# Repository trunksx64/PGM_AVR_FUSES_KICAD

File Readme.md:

# Restore AVR FUSES SMD ::: Revisión R1 :: Versión 1.10

## Razón de Ser e Inspiración

Este escudo para Arduino UNO se diseñó teniendo en mente inicialmente una forma para restaurar los FUSES del Atmega328P que por error u olvido se programaban mal en esta placa.
Haciendo inutilizables estos microcontroladores con programadores seriales como el AMTEL-ICE o MPLAB-SNAP, al inicio se diseñó como un simple restaurador, pero se vio la idea de dotarlo de más características como hacerlo un programador HIGH VOLTAJE, 
por lo cual se incluyo la etapa de elevación de tensión para obtener 12~14VDC, esta hizo que los pines disponibles del Arduino no fueran suficientes, se incluyo un expansor MCP23S08, para la comunicación de los Datos de 8Bits y el resto para el control de la programación en paralelo.
La idea a futuro es diseñar y crear una GUI multiplataforma para programar el Atmega328P y microcontroladores compatibles hacia abajo en número de pines.

## Características del Hardware

 * Socket ZIF de 28 Pines similar a la Marca 3M.
 * Expandor de puerto SPI MCP23S08.
 * Botones para Reset de la Placa UNO y Accion de programación.
 * Dos LEDS de estado de Programación.
 * Control de Alimentacion VCC y Elevador de Tensión para VPP.
 * Resistencias de protección, para evitar daño si el Microcontrolador es puesto al revez.
 * Diseño de Escudo (Shield) compatible con Arduino UNO R3.

## Características Específicas

Se tomó el Expansor MCP23S08, usando el protocolo SPI para garantizar la máxima velocidad de Datos para la Programación. 
El levador de tensión usa un juego de Diodo y Bobina simple, de fácil adquisición en el mercado con amplio valores sin problema alguno, todo esto implementado el control por PWM y ADC para controlar la estabilidad de la tensión de VPP para el microcontrolador.

## Versiones

* 2023 : 1.0.0 : Primera Versión.
* 2023 : 1.1.0 : Diseño de Liberias para Modelo 3D del Socket ZIF.

## ERRATAS

* Ninguna en el Momento.

## Créditos

xDNA Electronics & Desing es una microempresa Personal, que se dedica y encarga de elaborar proyectos de Control y Automatización por pedido, su idea es colaborar y ayudar a quines a si lo requieran, el proyecto se hizo principalmente como Hobby el cual gracias a terceros se pudo implementar y hacer su creación, por lo cual se da la libertad de usarlo para experimentar sin hacer uso comercial del mismo.

## Licencia

Licensed under Attribution-NonCommercial-ShareAlike 4.0 International (CC BY-NC-SA 4.0)

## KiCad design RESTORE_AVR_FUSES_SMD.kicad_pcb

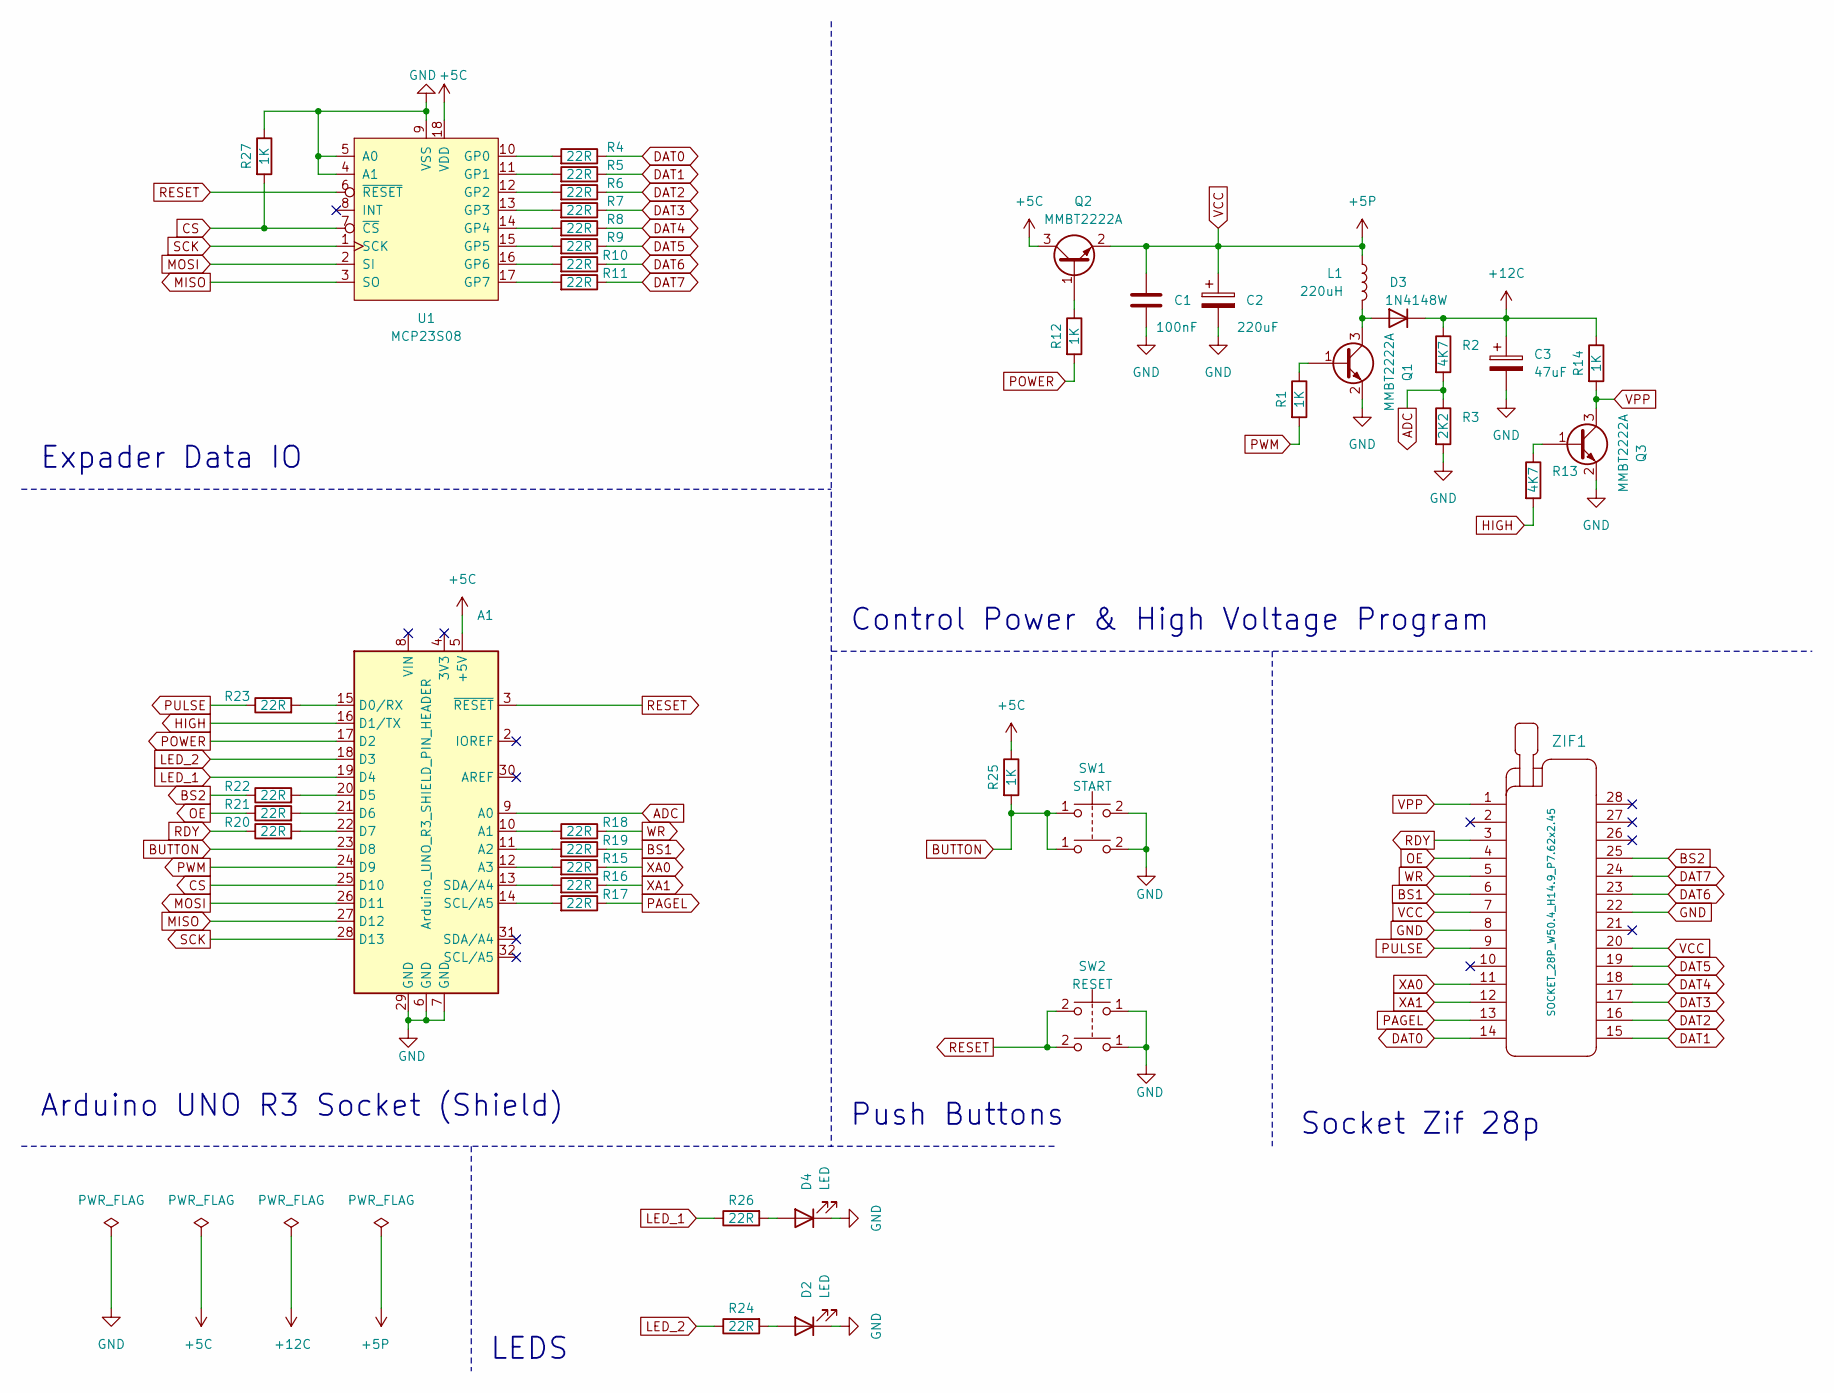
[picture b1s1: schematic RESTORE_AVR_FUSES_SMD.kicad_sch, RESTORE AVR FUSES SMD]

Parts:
A1: Arduino_UNO_R3_SHIELD_PIN_HEADER; x_Arduino_UNO_R3
C1: 100nF; C_1206_3216Metric
C2: 220uF; CP_Elec_6.3x5.2
C3: 47uF; CP_Elec_6.3x5.9
D2, D4: LED; LED_1210RVC
D3: 1N4148W; D_SOD-123
L1: 220uH; L_Sunlord_MWSA0402S
Q1, Q2, Q3: MMBT2222A; SOT-23
R1, R12, R14, R25, R27: 1K; R_1206_3216Metric_Pad1.30x1.75mm_HandSolder
R2, R13: 4K7; R_1206_3216Metric_Pad1.30x1.75mm_HandSolder
R3: 2K2; R_1206_3216Metric_Pad1.30x1.75mm_HandSolder
R4, R5, R6, R7, R8, R9, R10, R11, R15, R16, R17, R18, R19, R20, R21, R22, R23, R24, R26: 22R; R_1206_3216Metric_Pad1.30x1.75mm_HandSolder
SW1: START; SW_PUSH_6mm
SW2: RESET; SW_PUSH_6mm
U1: MCP23S08; SOIC-18W_7.5x11.6mm_P1.27mm
ZIF1: SOCKET_28P_W50.4_H14.9_P7.62x2.45

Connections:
+5C: A1.5 (+5V), Q2.3 (C), R25.1, U1.18 (VDD)
+12C: C3.1, D3.1 (K), R2.1, R14.1
ADC: A1.9 (A0), R2.2, R3.1
BS1: R19.1, ZIF1.6
BS2: R22.1, ZIF1.25
BUTTON: A1.23 (D8), R25.2, SW1.1
CS: A1.25 (D10), R27.2, U1.7 (~CS)
DAT0: R4.1, ZIF1.14
DAT1: R5.1, ZIF1.15
DAT2: R6.1, ZIF1.16
DAT3: R7.1, ZIF1.17
DAT4: R8.1, ZIF1.18
DAT5: R9.1, ZIF1.19
DAT6: R10.1, ZIF1.23
DAT7: R11.1, ZIF1.24
GND: A1.6 (GND), A1.7 (GND), A1.29 (GND), C1.2, C2.2, C3.2, D2.1 (K), D4.1 (K), Q1.2 (E), Q3.2 (E), R3.2, R27.1, SW1.2, SW2.1, U1.4 (A1), U1.5 (A0), U1.9 (VSS), ZIF1.8, ZIF1.22
HIGH: A1.16 (D1/TX), R13.2
LED_1: A1.19 (D4), R26.1
LED_2: A1.18 (D3), R24.1
MISO: A1.27 (D12), U1.3 (SO)
MOSI: A1.26 (D11), U1.2 (SI)
unnamed: A1.10 (A1), R18.2
unnamed: A1.11 (A2), R19.2
unnamed: A1.12 (A3), R15.2
unnamed: A1.15 (D0/RX), R23.2
unnamed: A1.20 (D5), R22.2
unnamed: A1.21 (D6), R21.2
unnamed: A1.22 (D7), R20.2
unnamed: A1.14 (SCL/A5), R17.2
unnamed: A1.13 (SDA/A4), R16.2
unnamed: D2.2 (A), R24.2
unnamed: D3.2 (A), L1.2, Q1.3 (C)
unnamed: D4.2 (A), R26.2
unnamed: Q1.1 (B), R1.1
unnamed: Q2.1 (B), R12.1
unnamed: Q3.1 (B), R13.1
unnamed: R4.2, U1.10 (GP0)
unnamed: R5.2, U1.11 (GP1)
unnamed: R6.2, U1.12 (GP2)
unnamed: R7.2, U1.13 (GP3)
unnamed: R8.2, U1.14 (GP4)
unnamed: R9.2, U1.15 (GP5)
unnamed: R10.2, U1.16 (GP6)
unnamed: R11.2, U1.17 (GP7)
OE: R21.1, ZIF1.4
PAGEL: R17.1, ZIF1.13
POWER: A1.17 (D2), R12.2
PULSE: R23.1, ZIF1.9
PWM: A1.24 (D9), R1.2
RDY: R20.1, ZIF1.3
RESET: A1.3 (~RESET), SW2.2 (4), U1.6 (~RESET)
SCK: A1.28 (D13), U1.1 (SCK)
VCC: C1.1, C2.1, L1.1, Q2.2 (E), ZIF1.7, ZIF1.20
VPP: Q3.3 (C), R14.2, ZIF1.1
WR: R18.1, ZIF1.5
XA0: R15.1, ZIF1.11
XA1: R16.1, ZIF1.12

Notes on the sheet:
Control Power & High Voltage Program
Arduino UNO R3 Socket (Shield)
Push Buttons
LEDS
Socket Zif 28p
Expader Data IO

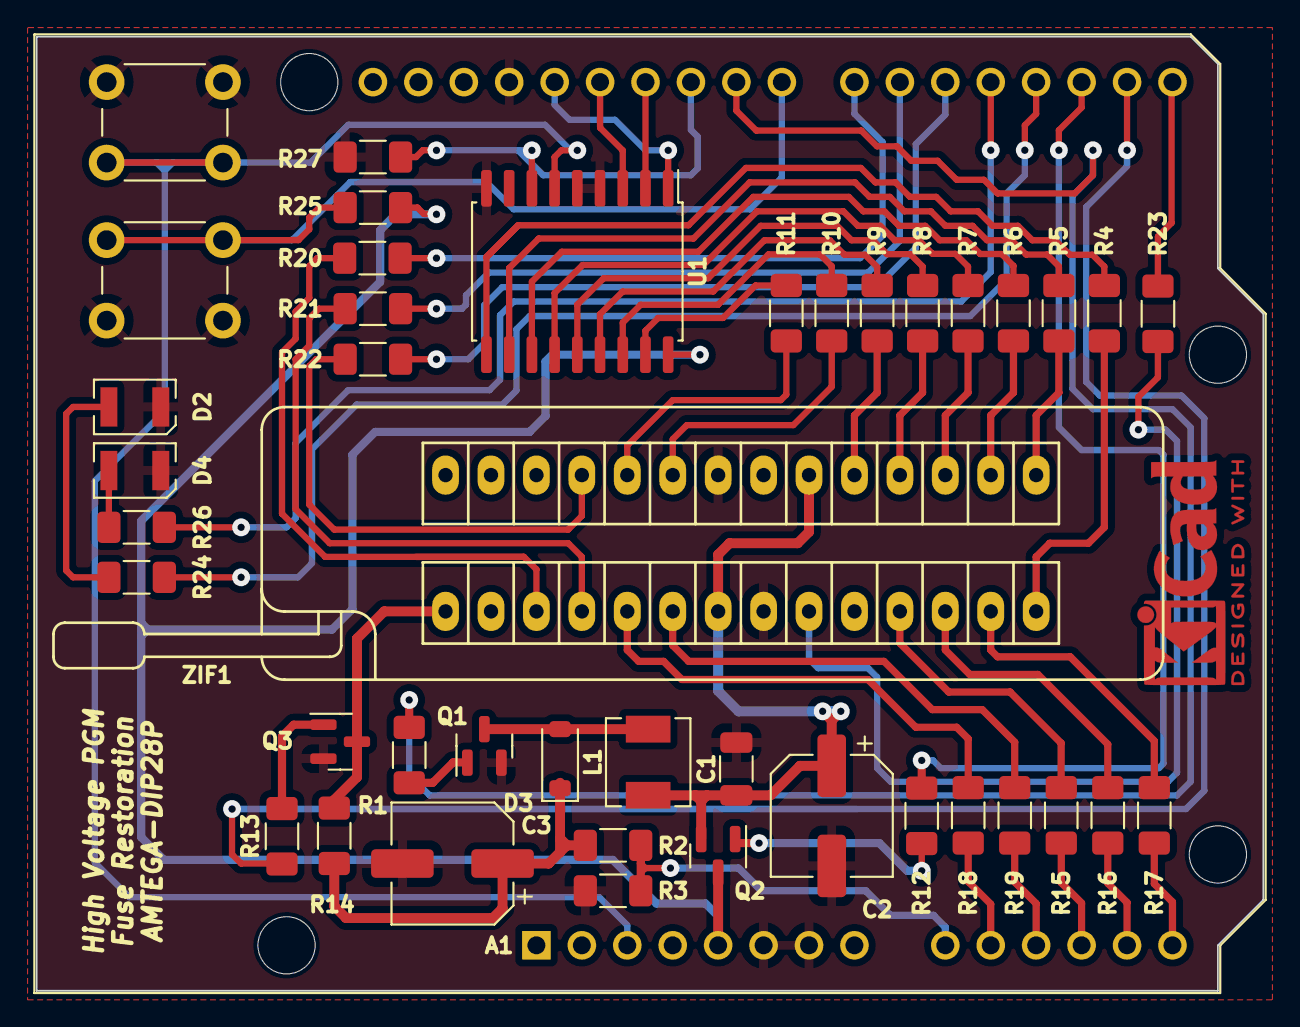
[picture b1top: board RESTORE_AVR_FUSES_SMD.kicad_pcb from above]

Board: 2 copper layers, 68.6 x 53.3 mm, 42 parts (0 on the bottom side), 57 nets.

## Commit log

2023-03-25 25/03/23/A
2023-12-26 26/12/13/A
